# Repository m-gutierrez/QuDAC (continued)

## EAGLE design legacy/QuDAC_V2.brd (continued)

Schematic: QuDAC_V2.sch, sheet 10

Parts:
C108, C111, C114, C116: 10uF; C0805
C109, C112, C113, C115, C117: 0.1uF; C0603
C110: CC0603; C0603
C118: 10pF; C0603
C119: 50pF; C0603
U18: AD5791BRUZ; SOP65P640X120-20N
U19: AD8676ARZ; SOIC127P600X175-8N

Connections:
+VPWR: C108.2, C109.2, C114.2, C115.2, U18.5 (VDD), U19.8 (V+); also elsewhere on the board
-VPWR: C111.2, C112.2, C116.2, C117.2, U18.18 (VSS), U19.4 (V-); also elsewhere on the board
ANALOG_REF: C113.1, U19.3 (+IN_A); also elsewhere on the board
DPWR: C110.2, U18.6 (~RESET), U18.7 (~CLR), U18.9 (VCC), U18.10 (IOVCC); also elsewhere on the board
GND: C108.1, C109.1, C110.1, C111.1, C112.1, C113.2, C114.1, C115.1, C116.1, C117.1, C119.1, U18.15 (DGND), U18.19 (AGND), U19.5 (+IN_B); also elsewhere on the board
LDAC: U18.8 (~LDAC); also elsewhere on the board
unnamed: U18.4 (VREFPF), U19.1 (OUT_A)
unnamed: U18.16 (VREFNF), U19.7 (OUT_B)
unnamed: U18.3 (VREFPS), U19.2 (-IN_A)
unnamed: U18.17 (VREFNS), U19.6 (-IN_B)
unnamed: C119.2, U18.2 (VOUT)
unnamed: C118.1, U18.1 (INV)
unnamed: C118.2, U18.20 (RFB)
SCLK_8: U18.13 (SCLK)
SDIN_8: U18.12 (SDIN)
SDO_8: U18.11 (SDO)
SYNC_8: U18.14 (~SYNC)

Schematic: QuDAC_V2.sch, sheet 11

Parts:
C120, C123, C126, C128: 10uF; C0805
C121, C124, C125, C127, C129: 0.1uF; C0603
C122: CC0603; C0603
C130: 10pF; C0603
C131: 50pF; C0603
U20: AD5791BRUZ; SOP65P640X120-20N
U21: AD8676ARZ; SOIC127P600X175-8N

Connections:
+VPWR: C120.2, C121.2, C126.2, C127.2, U20.5 (VDD), U21.8 (V+); also elsewhere on the board
-VPWR: C123.2, C124.2, C128.2, C129.2, U20.18 (VSS), U21.4 (V-); also elsewhere on the board
ANALOG_REF: C125.1, U21.3 (+IN_A); also elsewhere on the board
DPWR: C122.2, U20.6 (~RESET), U20.7 (~CLR), U20.9 (VCC), U20.10 (IOVCC); also elsewhere on the board
GND: C120.1, C121.1, C122.1, C123.1, C124.1, C125.2, C126.1, C127.1, C128.1, C129.1, C131.1, U20.15 (DGND), U20.19 (AGND), U21.5 (+IN_B); also elsewhere on the board
LDAC: U20.8 (~LDAC); also elsewhere on the board
unnamed: U20.4 (VREFPF), U21.1 (OUT_A)
unnamed: U20.16 (VREFNF), U21.7 (OUT_B)
unnamed: U20.3 (VREFPS), U21.2 (-IN_A)
unnamed: U20.17 (VREFNS), U21.6 (-IN_B)
unnamed: C131.2, U20.2 (VOUT)
unnamed: C130.1, U20.1 (INV)
unnamed: C130.2, U20.20 (RFB)
SCLK_9: U20.13 (SCLK)
SDIN_9: U20.12 (SDIN)
SDO_9: U20.11 (SDO)
SYNC_9: U20.14 (~SYNC)

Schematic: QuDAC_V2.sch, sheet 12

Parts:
C132, C135, C138, C140: 10uF; C0805
C133, C136, C137, C139, C141: 0.1uF; C0603
C134: CC0603; C0603
C142: 10pF; C0603
C143: 50pF; C0603
U22: AD5791BRUZ; SOP65P640X120-20N
U23: AD8676ARZ; SOIC127P600X175-8N

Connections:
+VPWR: C132.2, C133.2, C138.2, C139.2, U22.5 (VDD), U23.8 (V+); also elsewhere on the board
-VPWR: C135.2, C136.2, C140.2, C141.2, U22.18 (VSS), U23.4 (V-); also elsewhere on the board
ANALOG_REF: C137.1, U23.3 (+IN_A); also elsewhere on the board
DPWR: C134.2, U22.6 (~RESET), U22.7 (~CLR), U22.9 (VCC), U22.10 (IOVCC); also elsewhere on the board
GND: C132.1, C133.1, C134.1, C135.1, C136.1, C137.2, C138.1, C139.1, C140.1, C141.1, C143.1, U22.15 (DGND), U22.19 (AGND), U23.5 (+IN_B); also elsewhere on the board
LDAC: U22.8 (~LDAC); also elsewhere on the board
unnamed: U22.4 (VREFPF), U23.1 (OUT_A)
unnamed: U22.16 (VREFNF), U23.7 (OUT_B)
unnamed: U22.3 (VREFPS), U23.2 (-IN_A)
unnamed: U22.17 (VREFNS), U23.6 (-IN_B)
unnamed: C143.2, U22.2 (VOUT)
unnamed: C142.1, U22.1 (INV)
unnamed: C142.2, U22.20 (RFB)
SCLK_10: U22.13 (SCLK)
SDIN_10: U22.12 (SDIN)
SDO_10: U22.11 (SDO)
SYNC_10: U22.14 (~SYNC)

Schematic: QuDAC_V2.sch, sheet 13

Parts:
C144, C147, C150, C152: 10uF; C0805
C145, C148, C149, C151, C153: 0.1uF; C0603
C146: CC0603; C0603
C154: 10pF; C0603
C155: 50pF; C0603
U24: AD5791BRUZ; SOP65P640X120-20N
U25: AD8676ARZ; SOIC127P600X175-8N

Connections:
+VPWR: C144.2, C145.2, C150.2, C151.2, U24.5 (VDD), U25.8 (V+); also elsewhere on the board
-VPWR: C147.2, C148.2, C152.2, C153.2, U24.18 (VSS), U25.4 (V-); also elsewhere on the board
ANALOG_REF: C149.1, U25.3 (+IN_A); also elsewhere on the board
DPWR: C146.2, U24.6 (~RESET), U24.7 (~CLR), U24.9 (VCC), U24.10 (IOVCC); also elsewhere on the board
GND: C144.1, C145.1, C146.1, C147.1, C148.1, C149.2, C150.1, C151.1, C152.1, C153.1, C155.1, U24.15 (DGND), U24.19 (AGND), U25.5 (+IN_B); also elsewhere on the board
LDAC: U24.8 (~LDAC); also elsewhere on the board
unnamed: U24.4 (VREFPF), U25.1 (OUT_A)
unnamed: U24.16 (VREFNF), U25.7 (OUT_B)
unnamed: U24.3 (VREFPS), U25.2 (-IN_A)
unnamed: U24.17 (VREFNS), U25.6 (-IN_B)
unnamed: C155.2, U24.2 (VOUT)
unnamed: C154.1, U24.1 (INV)
unnamed: C154.2, U24.20 (RFB)
SCLK_11: U24.13 (SCLK)
SDIN_11: U24.12 (SDIN)
SDO_11: U24.11 (SDO)
SYNC_11: U24.14 (~SYNC)

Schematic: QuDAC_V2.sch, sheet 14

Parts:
C156, C159, C162, C164: 10uF; C0805
C157, C160, C161, C163, C165: 0.1uF; C0603
C158: CC0603; C0603
C166: 10pF; C0603
C167: 50pF; C0603
U26: AD5791BRUZ; SOP65P640X120-20N
U27: AD8676ARZ; SOIC127P600X175-8N

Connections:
+VPWR: C156.2, C157.2, C162.2, C163.2, U26.5 (VDD), U27.8 (V+); also elsewhere on the board
-VPWR: C159.2, C160.2, C164.2, C165.2, U26.18 (VSS), U27.4 (V-); also elsewhere on the board
ANALOG_REF: C161.1, U27.3 (+IN_A); also elsewhere on the board
DPWR: C158.2, U26.6 (~RESET), U26.7 (~CLR), U26.9 (VCC), U26.10 (IOVCC); also elsewhere on the board
GND: C156.1, C157.1, C158.1, C159.1, C160.1, C161.2, C162.1, C163.1, C164.1, C165.1, C167.1, U26.15 (DGND), U26.19 (AGND), U27.5 (+IN_B); also elsewhere on the board
LDAC: U26.8 (~LDAC); also elsewhere on the board
unnamed: U26.4 (VREFPF), U27.1 (OUT_A)
unnamed: U26.16 (VREFNF), U27.7 (OUT_B)
unnamed: U26.3 (VREFPS), U27.2 (-IN_A)
unnamed: U26.17 (VREFNS), U27.6 (-IN_B)
unnamed: C167.2, U26.2 (VOUT)
unnamed: C166.1, U26.1 (INV)
unnamed: C166.2, U26.20 (RFB)
SCLK_12: U26.13 (SCLK)
SDIN_12: U26.12 (SDIN)
SDO_12: U26.11 (SDO)
SYNC_12: U26.14 (~SYNC)

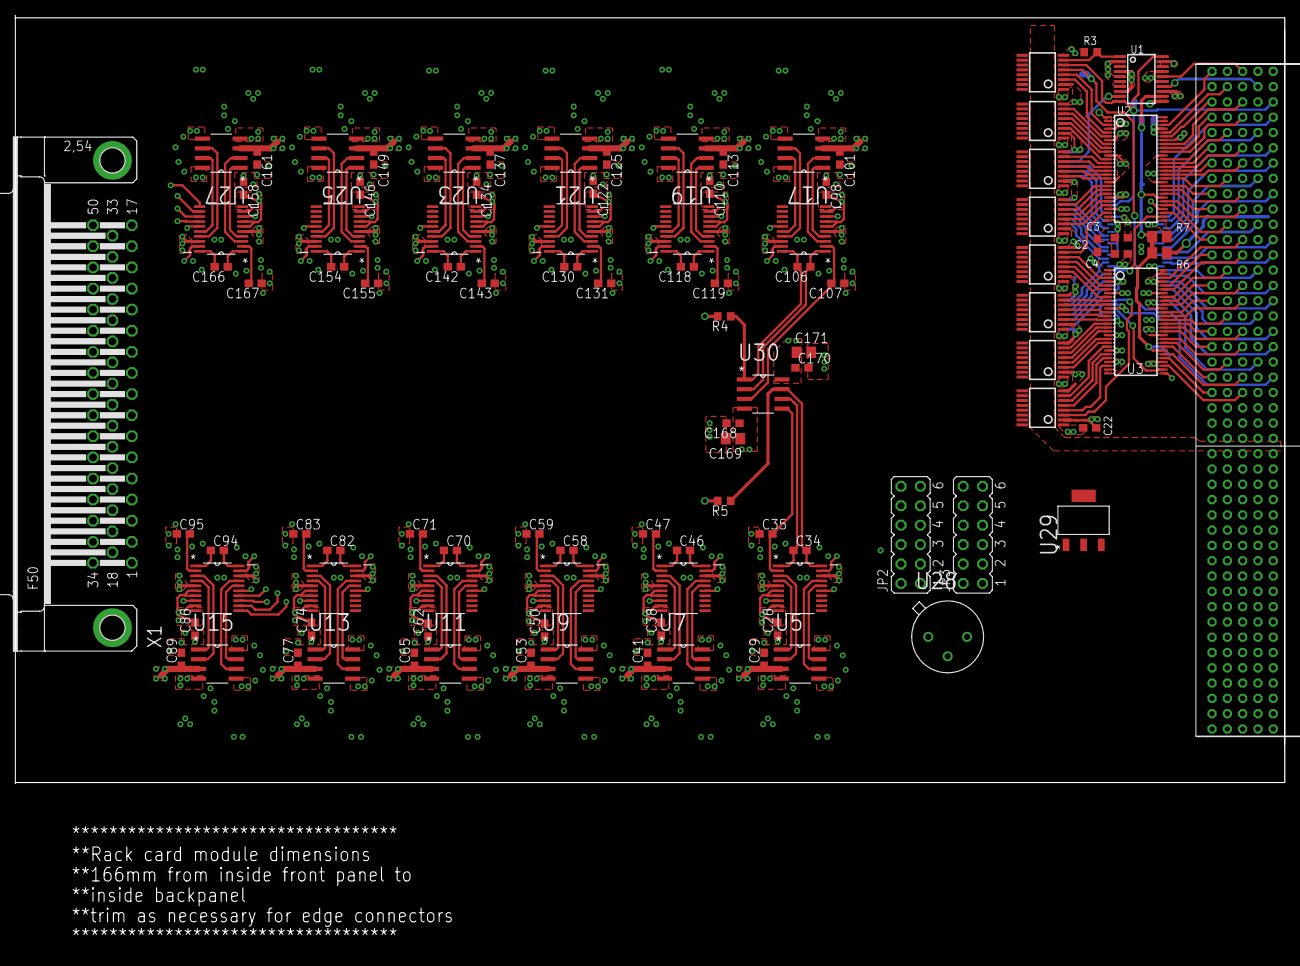
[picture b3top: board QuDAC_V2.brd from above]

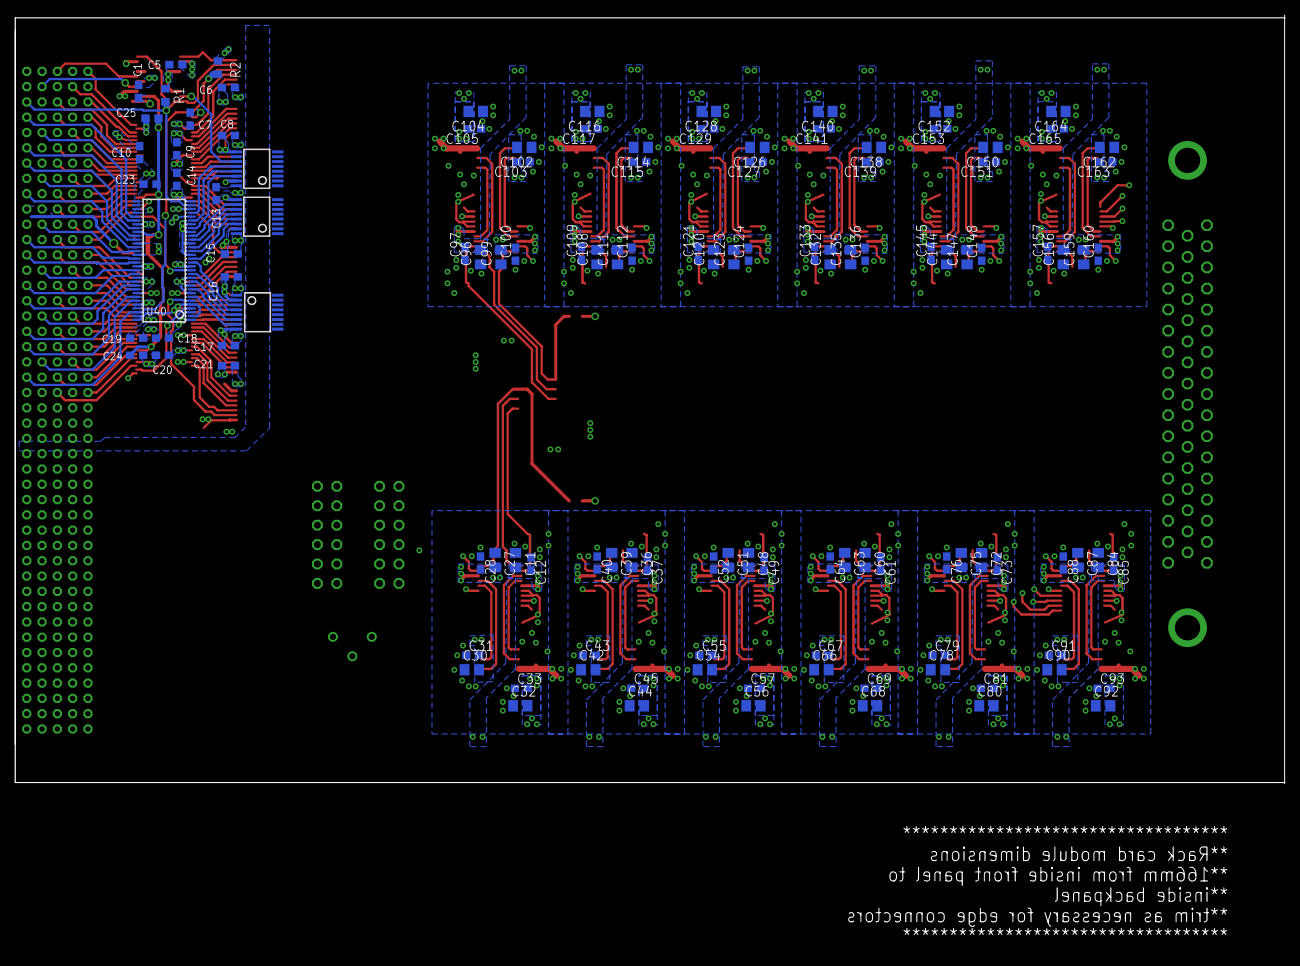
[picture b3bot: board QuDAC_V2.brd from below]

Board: 6 copper layers, 166.0 x 100.5 mm, 224 parts (121 on the bottom side), 209 nets.

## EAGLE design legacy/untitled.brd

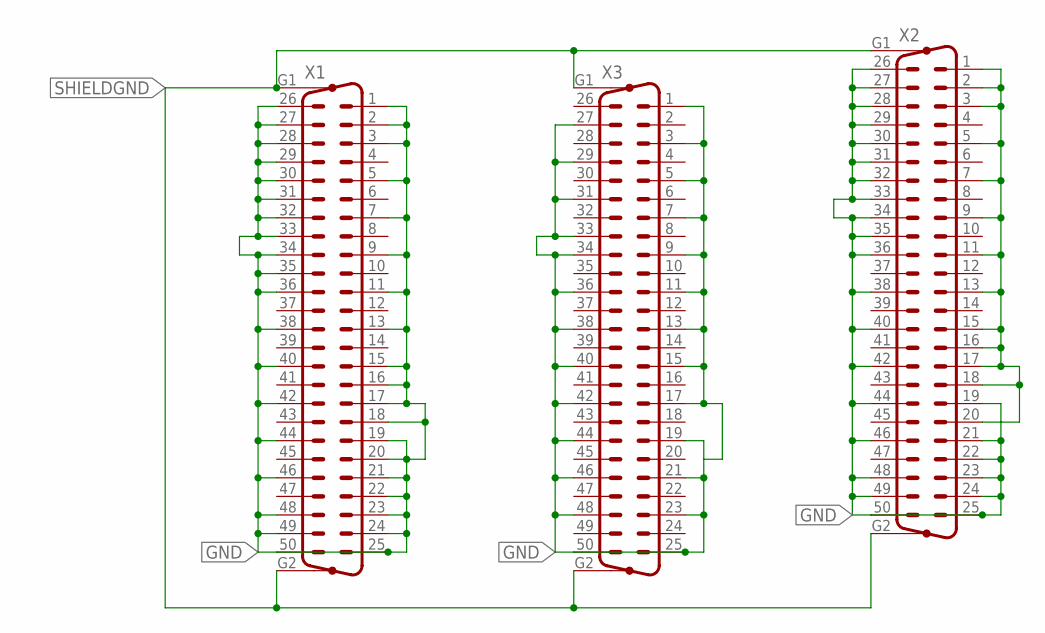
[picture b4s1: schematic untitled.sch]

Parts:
X1, X2, X3: M50VP

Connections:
GND: X1.1, X1.2, X1.3, X1.5, X1.7, X1.9, X1.11, X1.13, X1.15, X1.16, X1.17, X1.18, X1.19, X1.20, X1.21, X1.22, X1.23, X1.24, X1.25, X1.26, X1.27, X1.28, X1.29, X1.30, X1.31, X1.32, X1.33, X1.34, X1.35, X1.36, X1.38, X1.40, X1.42, X1.44, X1.46, X1.48, X1.49, X1.50, X2.1, X2.2, X2.3, X2.5, X2.7, X2.9, X2.11, X2.13, X2.15, X2.16, X2.17, X2.18, X2.19, X2.20, X2.21, X2.22, X2.23, X2.24, X2.25, X2.26, X2.27, X2.28, X2.29, X2.30, X2.31, X2.32, X2.33, X2.34, X2.35, X2.36, X2.38, X2.40, X2.42, X2.44, X2.46, X2.48, X2.49, X2.50, X3.1, X3.3, X3.5, X3.7, X3.9, X3.11, X3.13, X3.15, X3.17, X3.19, X3.21, X3.23, X3.25, X3.27, X3.29, X3.31, X3.33, X3.34, X3.36, X3.38, X3.40, X3.42, X3.44, X3.46, X3.48, X3.50
SHIELDGND: X1.G1, X1.G2, X2.G1, X2.G2, X3.G1, X3.G2

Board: 2 copper layers, 3 parts (2 on the bottom side), 2 nets, no tracks yet.

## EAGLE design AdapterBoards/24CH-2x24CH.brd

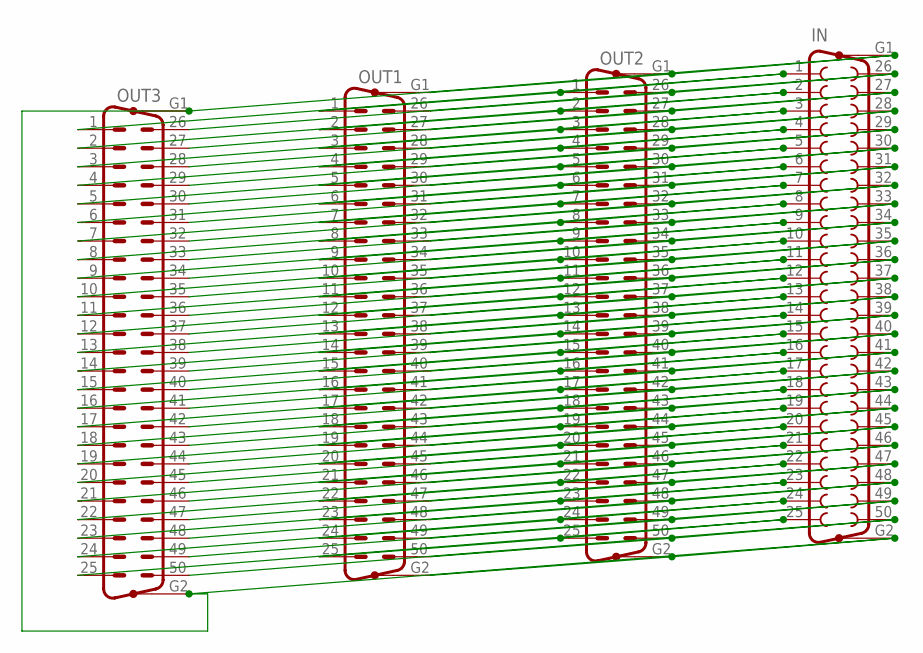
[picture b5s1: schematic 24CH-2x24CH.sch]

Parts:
IN: F50VP
OUT1, OUT2, OUT3: M50VP

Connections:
GND1: IN.G1, IN.G2, OUT1.G1, OUT1.G2, OUT2.G1, OUT2.G2, OUT3.G1, OUT3.G2
unnamed: IN.35, OUT1.35, OUT2.35, OUT3.35
unnamed: IN.38, OUT1.38, OUT2.38, OUT3.38
unnamed: IN.1, OUT1.1, OUT2.1, OUT3.1
unnamed: IN.18, OUT1.18, OUT2.18, OUT3.18
unnamed: IN.2, OUT1.2, OUT2.2, OUT3.2
unnamed: IN.19, OUT1.19, OUT2.19, OUT3.19
unnamed: IN.3, OUT1.3, OUT2.3, OUT3.3
unnamed: IN.20, OUT1.20, OUT2.20, OUT3.20
unnamed: IN.4, OUT1.4, OUT2.4, OUT3.4
unnamed: IN.21, OUT1.21, OUT2.21, OUT3.21
unnamed: IN.5, OUT1.5, OUT2.5, OUT3.5
unnamed: IN.22, OUT1.22, OUT2.22, OUT3.22
unnamed: IN.6, OUT1.6, OUT2.6, OUT3.6
unnamed: IN.23, OUT1.23, OUT2.23, OUT3.23
unnamed: IN.7, OUT1.7, OUT2.7, OUT3.7
unnamed: IN.24, OUT1.24, OUT2.24, OUT3.24
unnamed: IN.8, OUT1.8, OUT2.8, OUT3.8
unnamed: IN.25, OUT1.25, OUT2.25, OUT3.25
unnamed: IN.9, OUT1.9, OUT2.9, OUT3.9
unnamed: IN.26, OUT1.26, OUT2.26, OUT3.26
unnamed: IN.10, OUT1.10, OUT2.10, OUT3.10
unnamed: IN.27, OUT1.27, OUT2.27, OUT3.27
unnamed: IN.11, OUT1.11, OUT2.11, OUT3.11
unnamed: IN.28, OUT1.28, OUT2.28, OUT3.28
unnamed: IN.12, OUT1.12, OUT2.12, OUT3.12
unnamed: IN.29, OUT1.29, OUT2.29, OUT3.29
unnamed: IN.13, OUT1.13, OUT2.13, OUT3.13
unnamed: IN.30, OUT1.30, OUT2.30, OUT3.30
unnamed: IN.14, OUT1.14, OUT2.14, OUT3.14
unnamed: IN.31, OUT1.31, OUT2.31, OUT3.31
unnamed: IN.15, OUT1.15, OUT2.15, OUT3.15
unnamed: IN.32, OUT1.32, OUT2.32, OUT3.32
unnamed: IN.16, OUT1.16, OUT2.16, OUT3.16
unnamed: IN.33, OUT1.33, OUT2.33, OUT3.33
unnamed: IN.17, OUT1.17, OUT2.17, OUT3.17
unnamed: IN.40, OUT1.40, OUT2.40, OUT3.40
unnamed: IN.39, OUT1.39, OUT2.39, OUT3.39
unnamed: IN.34, OUT1.34, OUT2.34, OUT3.34
unnamed: IN.36, OUT1.36, OUT2.36, OUT3.36
unnamed: IN.37, OUT1.37, OUT2.37, OUT3.37
unnamed: IN.41, OUT1.41, OUT2.41, OUT3.41
unnamed: IN.42, OUT1.42, OUT2.42, OUT3.42
unnamed: IN.43, OUT1.43, OUT2.43, OUT3.43
unnamed: IN.44, OUT1.44, OUT2.44, OUT3.44
unnamed: IN.45, OUT1.45, OUT2.45, OUT3.45
unnamed: IN.46, OUT1.46, OUT2.46, OUT3.46
unnamed: IN.47, OUT1.47, OUT2.47, OUT3.47
unnamed: IN.48, OUT1.48, OUT2.48, OUT3.48
unnamed: IN.49, OUT1.49, OUT2.49, OUT3.49
unnamed: IN.50, OUT1.50, OUT2.50, OUT3.50

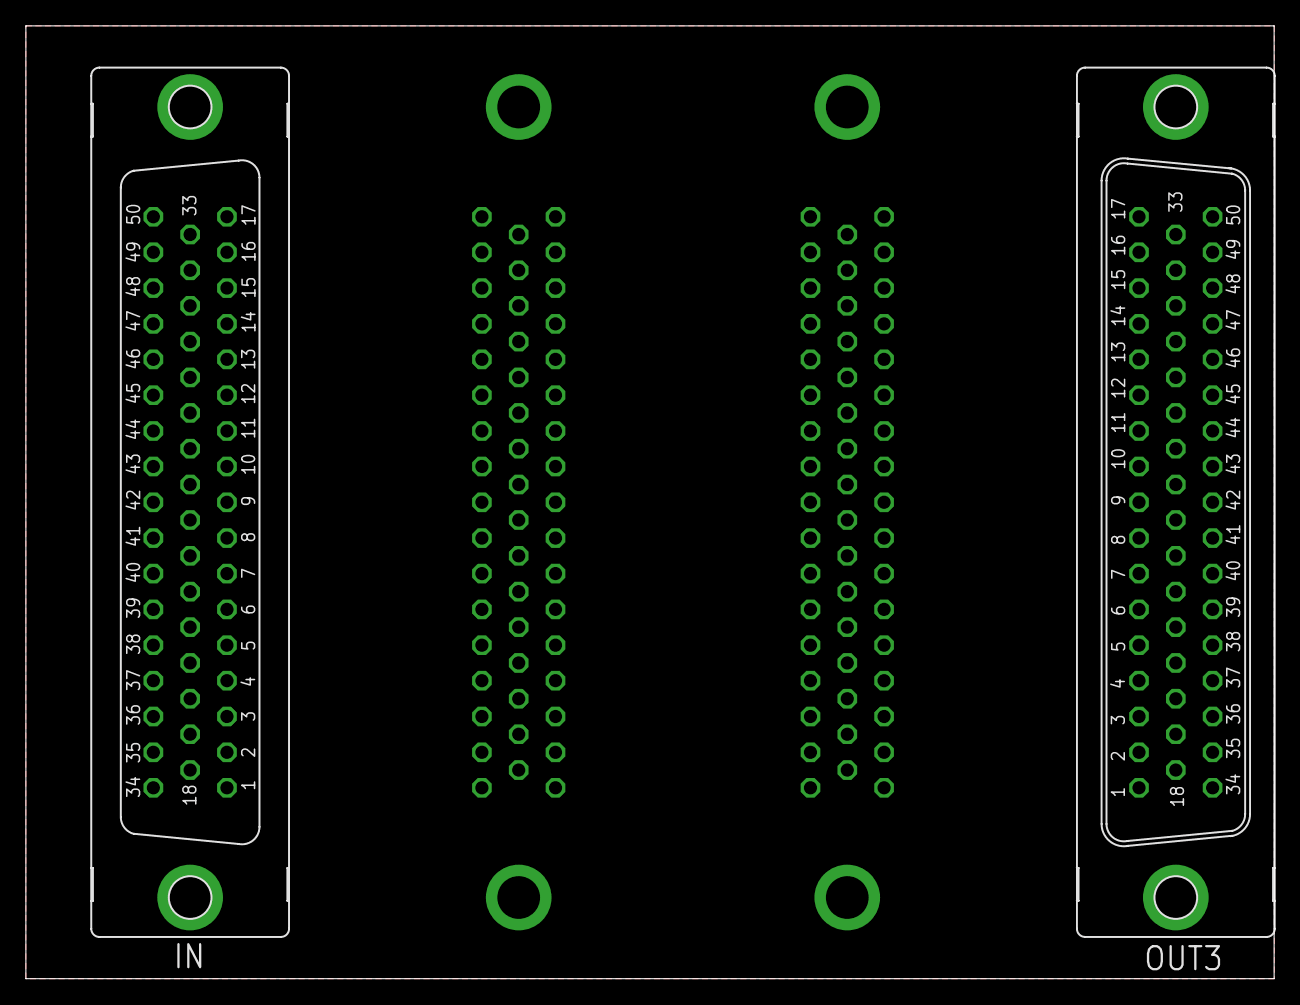
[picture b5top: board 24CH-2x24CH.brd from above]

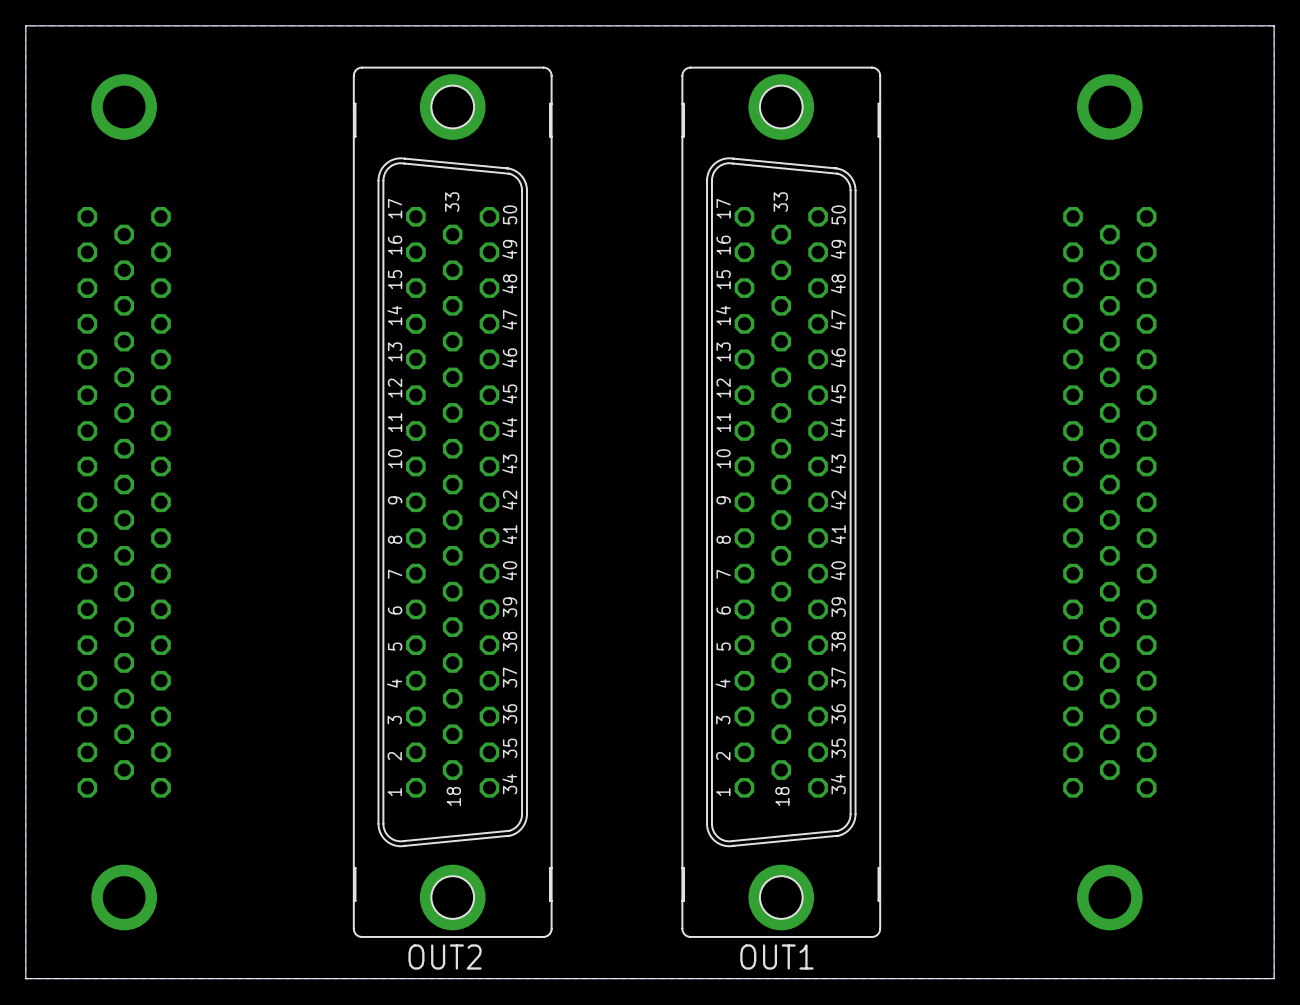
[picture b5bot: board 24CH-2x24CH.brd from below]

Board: 4 copper layers, 96.5 x 73.7 mm, 4 parts (2 on the bottom side), 51 nets.

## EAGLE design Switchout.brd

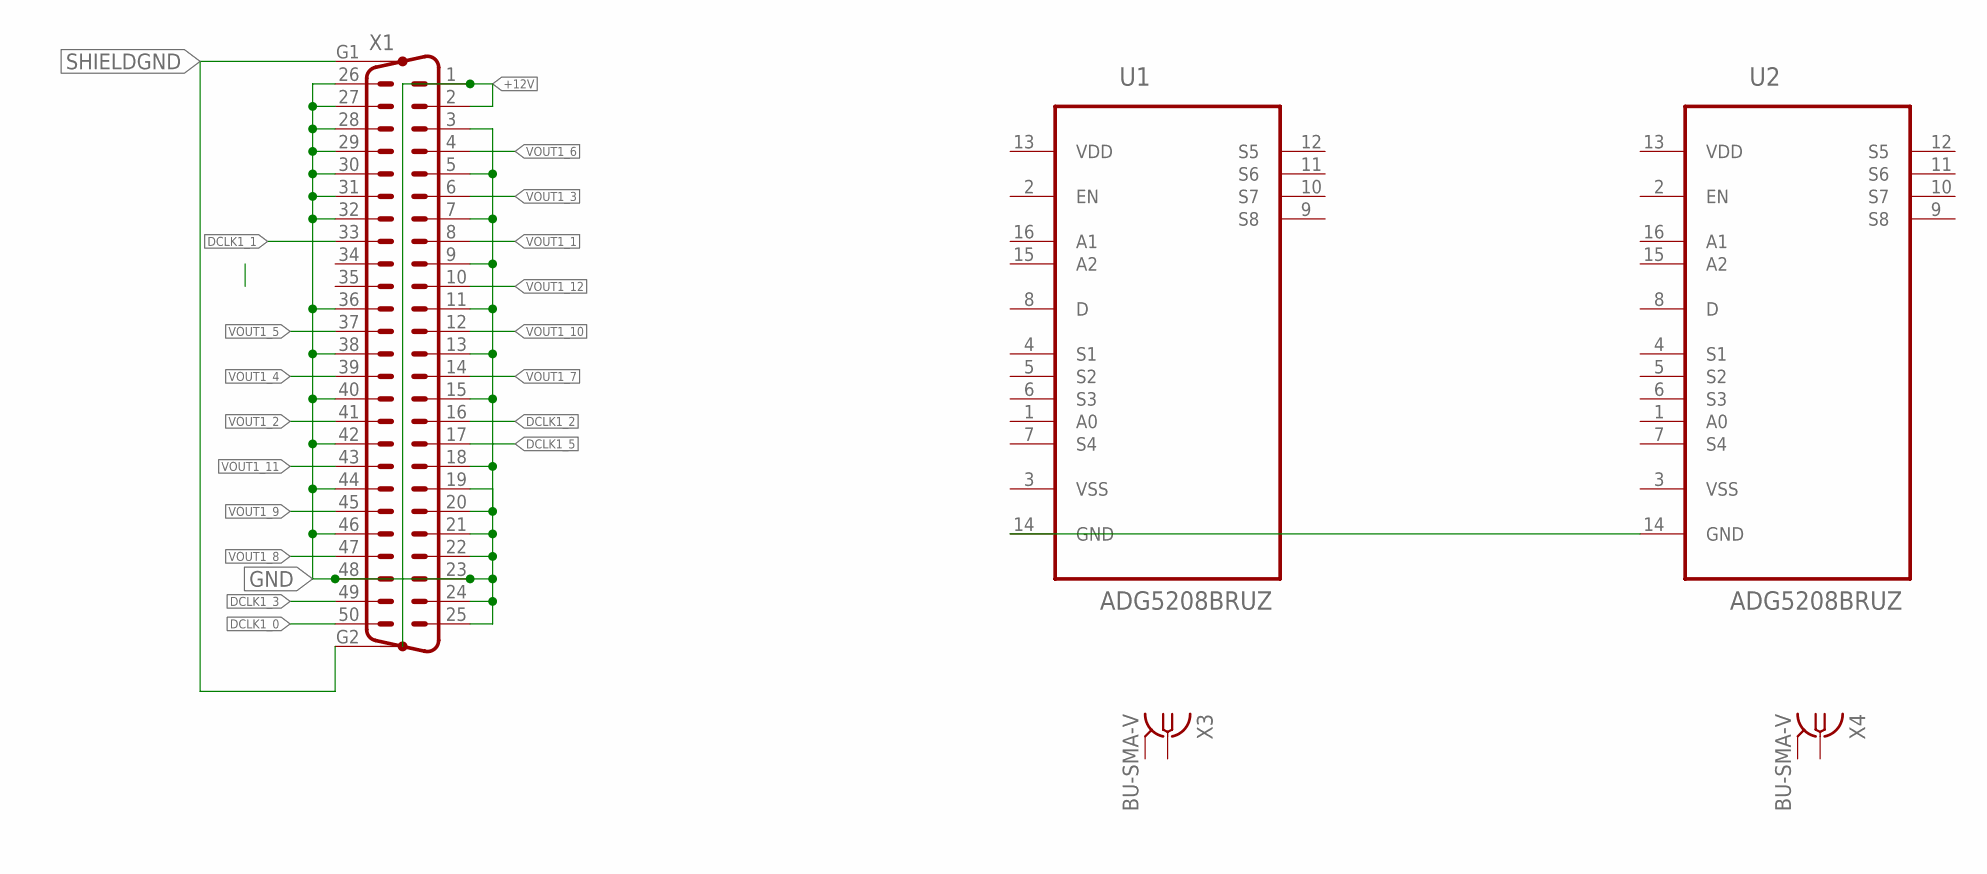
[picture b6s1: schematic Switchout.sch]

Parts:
U1, U2: ADG5208BRUZ; SOP65P640X120-16N
X1: M50VP
X3, X4: BU-SMA-V

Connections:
+12V: X1.1, X1.2
DCLK1_0: X1.50
DCLK1_1: X1.33
DCLK1_2: X1.16
DCLK1_3: X1.49
DCLK1_5: X1.17
GND: X1.3, X1.5, X1.7, X1.9, X1.11, X1.13, X1.15, X1.18, X1.19, X1.20, X1.21, X1.22, X1.23, X1.24, X1.25, X1.26, X1.27, X1.28, X1.29, X1.30, X1.31, X1.32, X1.36, X1.38, X1.40, X1.42, X1.44, X1.46, X1.48
unnamed: U1.14 (GND), U2.14 (GND)
SHIELDGND: X1.G1, X1.G2
VDD: U1.13 (VDD), U2.13 (VDD)
VOUT1_1: X1.8
VOUT1_2: X1.41
VOUT1_3: X1.6
VOUT1_4: X1.39
VOUT1_5: X1.37
VOUT1_6: X1.4
VOUT1_7: X1.14
VOUT1_8: X1.47
VOUT1_9: X1.45
VOUT1_10: X1.12
VOUT1_11: X1.43
VOUT1_12: X1.10
VSS: U1.3 (VSS), U2.3 (VSS)

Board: 2 copper layers, 5 parts (1 on the bottom side), 6 nets, no tracks yet.

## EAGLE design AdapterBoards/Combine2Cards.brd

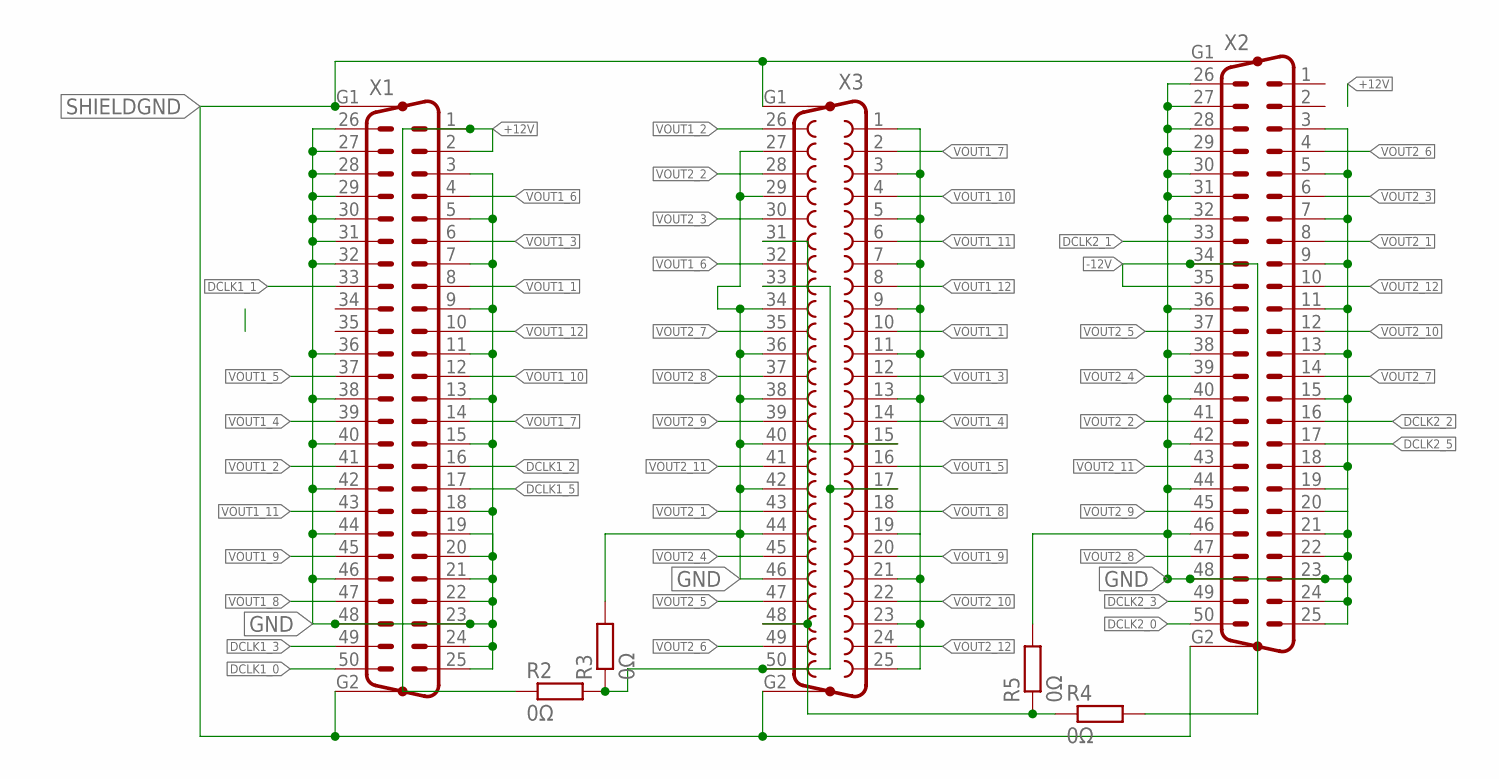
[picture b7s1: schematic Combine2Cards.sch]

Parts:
R2, R3, R4, R5: 0Ω; R0603
X1, X2: M50VP
X3: F50VP

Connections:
+12V: R2.1, X1.1, X1.2
-12V: R4.2, X2.34, X2.35
DCLK1_0: X1.50
DCLK1_1: X1.33
DCLK1_2: X1.16
DCLK1_3: X1.49
DCLK1_5: X1.17
DCLK2_0: X2.50
DCLK2_1: X2.33
DCLK2_2: X2.16
DCLK2_3: X2.49
DCLK2_5: X2.17
GND: R3.2, R5.2, X1.3, X1.5, X1.7, X1.9, X1.11, X1.13, X1.15, X1.18, X1.19, X1.20, X1.21, X1.22, X1.23, X1.24, X1.25, X1.26, X1.27, X1.28, X1.29, X1.30, X1.31, X1.32, X1.36, X1.38, X1.40, X1.42, X1.44, X1.46, X1.48, X2.3, X2.5, X2.7, X2.9, X2.11, X2.13, X2.15, X2.18, X2.19, X2.20, X2.21, X2.22, X2.23, X2.24, X2.25, X2.26, X2.27, X2.28, X2.29, X2.30, X2.31, X2.32, X2.36, X2.38, X2.40, X2.42, X2.44, X2.46, X2.48, X3.1, X3.3, X3.5, X3.7, X3.9, X3.11, X3.13, X3.19, X3.21, X3.23, X3.25, X3.27, X3.29, X3.34, X3.36, X3.38, X3.40, X3.42, X3.44, X3.46
unnamed: R2.2, R3.1, X3.17, X3.33, X3.50
unnamed: R4.1, R5.1, X3.15, X3.31, X3.48
SHIELDGND: X1.G1, X1.G2, X2.G1, X2.G2, X3.G1, X3.G2
VOUT1_1: X1.8, X3.10
VOUT1_2: X1.41, X3.26
VOUT1_3: X1.6, X3.12
VOUT1_4: X1.39, X3.14
VOUT1_5: X1.37, X3.16
VOUT1_6: X1.4, X3.32
VOUT1_7: X1.14, X3.2
VOUT1_8: X1.47, X3.18
VOUT1_9: X1.45, X3.20
VOUT1_10: X1.12, X3.4
VOUT1_11: X1.43, X3.6
VOUT1_12: X1.10, X3.8
VOUT2_1: X2.8, X3.43
VOUT2_2: X2.41, X3.28
VOUT2_3: X2.6, X3.30
VOUT2_4: X2.39, X3.45
VOUT2_5: X2.37, X3.47
VOUT2_6: X2.4, X3.49
VOUT2_7: X2.14, X3.35
VOUT2_8: X2.47, X3.37
VOUT2_9: X2.45, X3.39
VOUT2_10: X2.12, X3.22
VOUT2_11: X2.43, X3.41
VOUT2_12: X2.10, X3.24

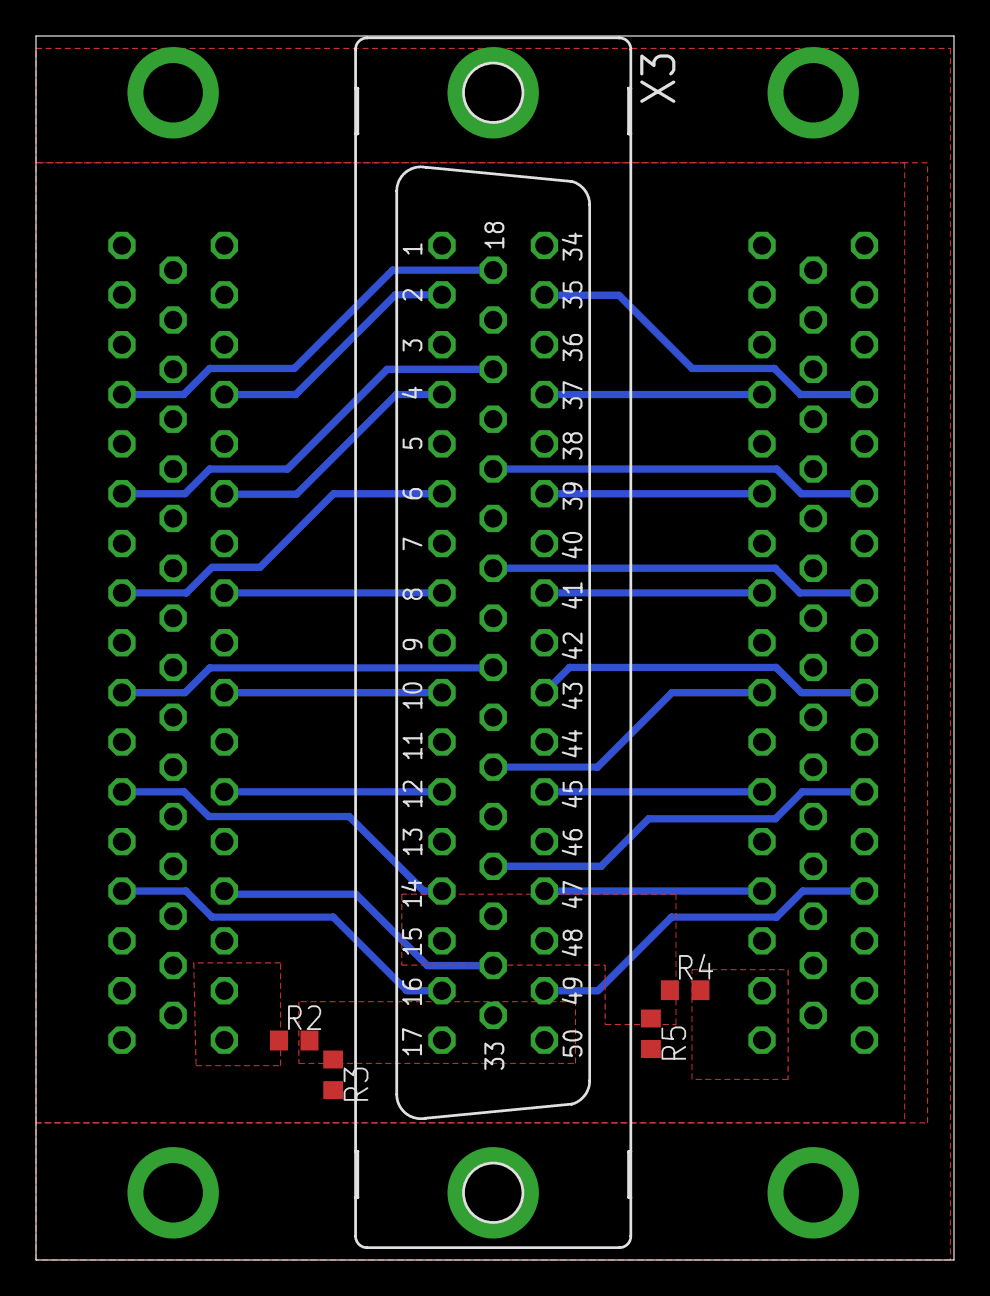
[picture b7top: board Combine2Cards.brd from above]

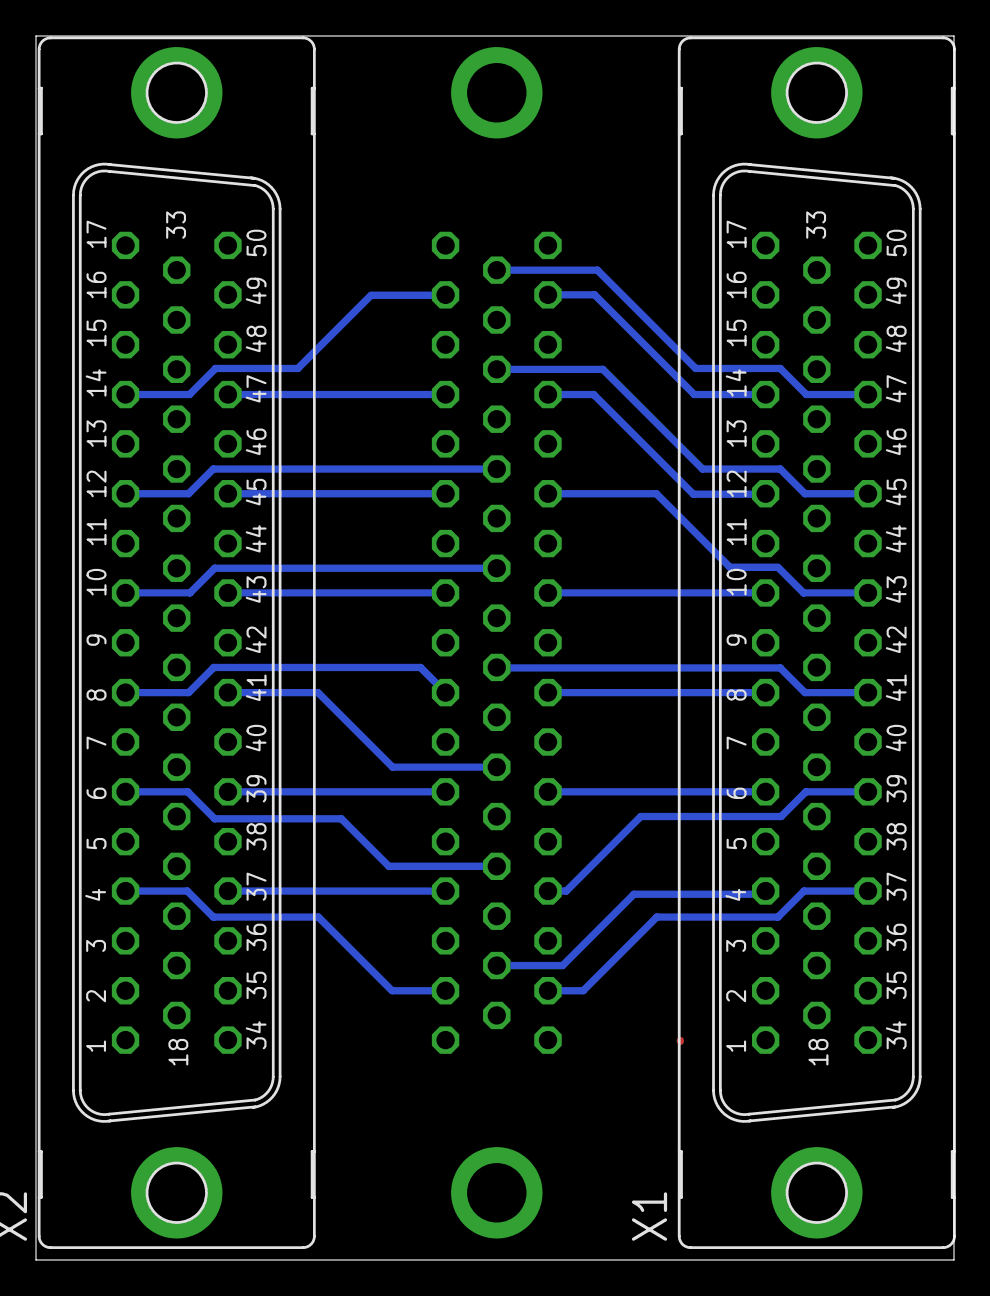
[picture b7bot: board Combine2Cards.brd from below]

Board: 2 copper layers, 51.0 x 68.0 mm, 7 parts (2 on the bottom side), 30 nets.
